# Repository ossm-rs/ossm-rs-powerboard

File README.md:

# OSSM-RS Powerboard

Power management PCB for AIM family motors, designed to pair with the Industrial ESP32-S3-RS485-CAN control board by Waveshare and run with OSSM-RS software.

This board is inspired by and builds on the OSSM hardware concept from KinkyMakers:
- OSSM-RS software: https://github.com/ossm-rs/ossm
- Original OSSM hardware/research: https://github.com/KinkyMakers/OSSM-hardware/tree/main

## What This Board Does

- Accepts DC input from an external power supply.
- Provides 24-36v output for the servo motor.
- Protects from back EMF.
- Provides regulated 12V output for the controller board.
- Supports two input connector variants in this repository:
	- C6P input variant (Molex-style connector).
	- R7BF input variant (barrel jack style, Kycon KPJX-4S).

## System

- Motor family:
	- 60aim40F
	- 57aim30
- Controller:
	- Waveshare Industrial ESP32-S3-RS485-CAN
- PSU
    - Meanwell GST220A36-R7BF
    - Meanwell GST360A36-C6P

Other motor configurations that use 24-36V may also work, but they have not been validated on this board yet.

## Board Variants

- C6P variant:
	- Input connector: C6P 6 Pin Molex footprint
	- Fabrication files prefix: `C6P_*`
	- STEP model: `STEP/powerboard-C6P.step`
- R7BF variant:
	- Input connector: R7BF KPJX-4S footprint
	- Fabrication files prefix: `R7BF_*`
	- STEP model: `STEP/powerboard-R7BF.step`

Do not populate both input connector styles on the same board.

## Usage

- External PSU (C6P or R7BF style) feeds the selected DC-IN connector on this board.
- Motor power is provided at the Motor Power output terminal.
- 12V and GND for the Waveshare board are provided at the ESP/CAN power terminal.
- Motor control and comms (CAN/RS485) are handled by the Waveshare board and motor harness.
- Configure and run OSSM-RS from https://github.com/ossm-rs/ossm.

Use the wiring diagram image below and verify polarity before first power-up.

## Manufacturing

For assembly orders, use files in `jlcpcb-fabrication-files/`:
- `*_bom.csv` for component list
- `*_positions.csv` for pick-and-place positions

This project is intended for small community group buys through JLCPCB (or another PCB manufacturer). As of 2026-03-17, a typical minimum order on JLCPCB is 5 boards and costs about EUR 100 total.

Estimated cost per board:
- PCB-only share: about EUR 20 per board (EUR 100 / 5)
- With shipping split across 5 boards: about (EUR 100 + shipping) / 5 per board

## Safety Notes

- This is a high-current motor power board; incorrect wiring can damage electronics.
- Always verify connector pinout/polarity against schematic and wiring diagrams.
- Keep wiring secure and strain-relieved.

## Credits

- OSSM-RS maintainers and contributors
- KinkyMakers OSSM hardware project and community research

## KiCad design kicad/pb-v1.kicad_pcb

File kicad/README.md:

# KiCad Project

Primary design source for the OSSM-RS powerboard.

## Main Files

- `pb-v1.kicad_sch`: Schematic
- `pb-v1.kicad_pcb`: PCB layout
- `pb-v1.kicad_pro`: KiCad project file
- `pb-v1.csv`: Consolidated BOM/export snapshot

## Project Libraries

- `project_symbols/`: Custom symbol libraries
- `project_footprints/`: Custom footprints
- `project_3dshapes/`: 3D models used by footprints

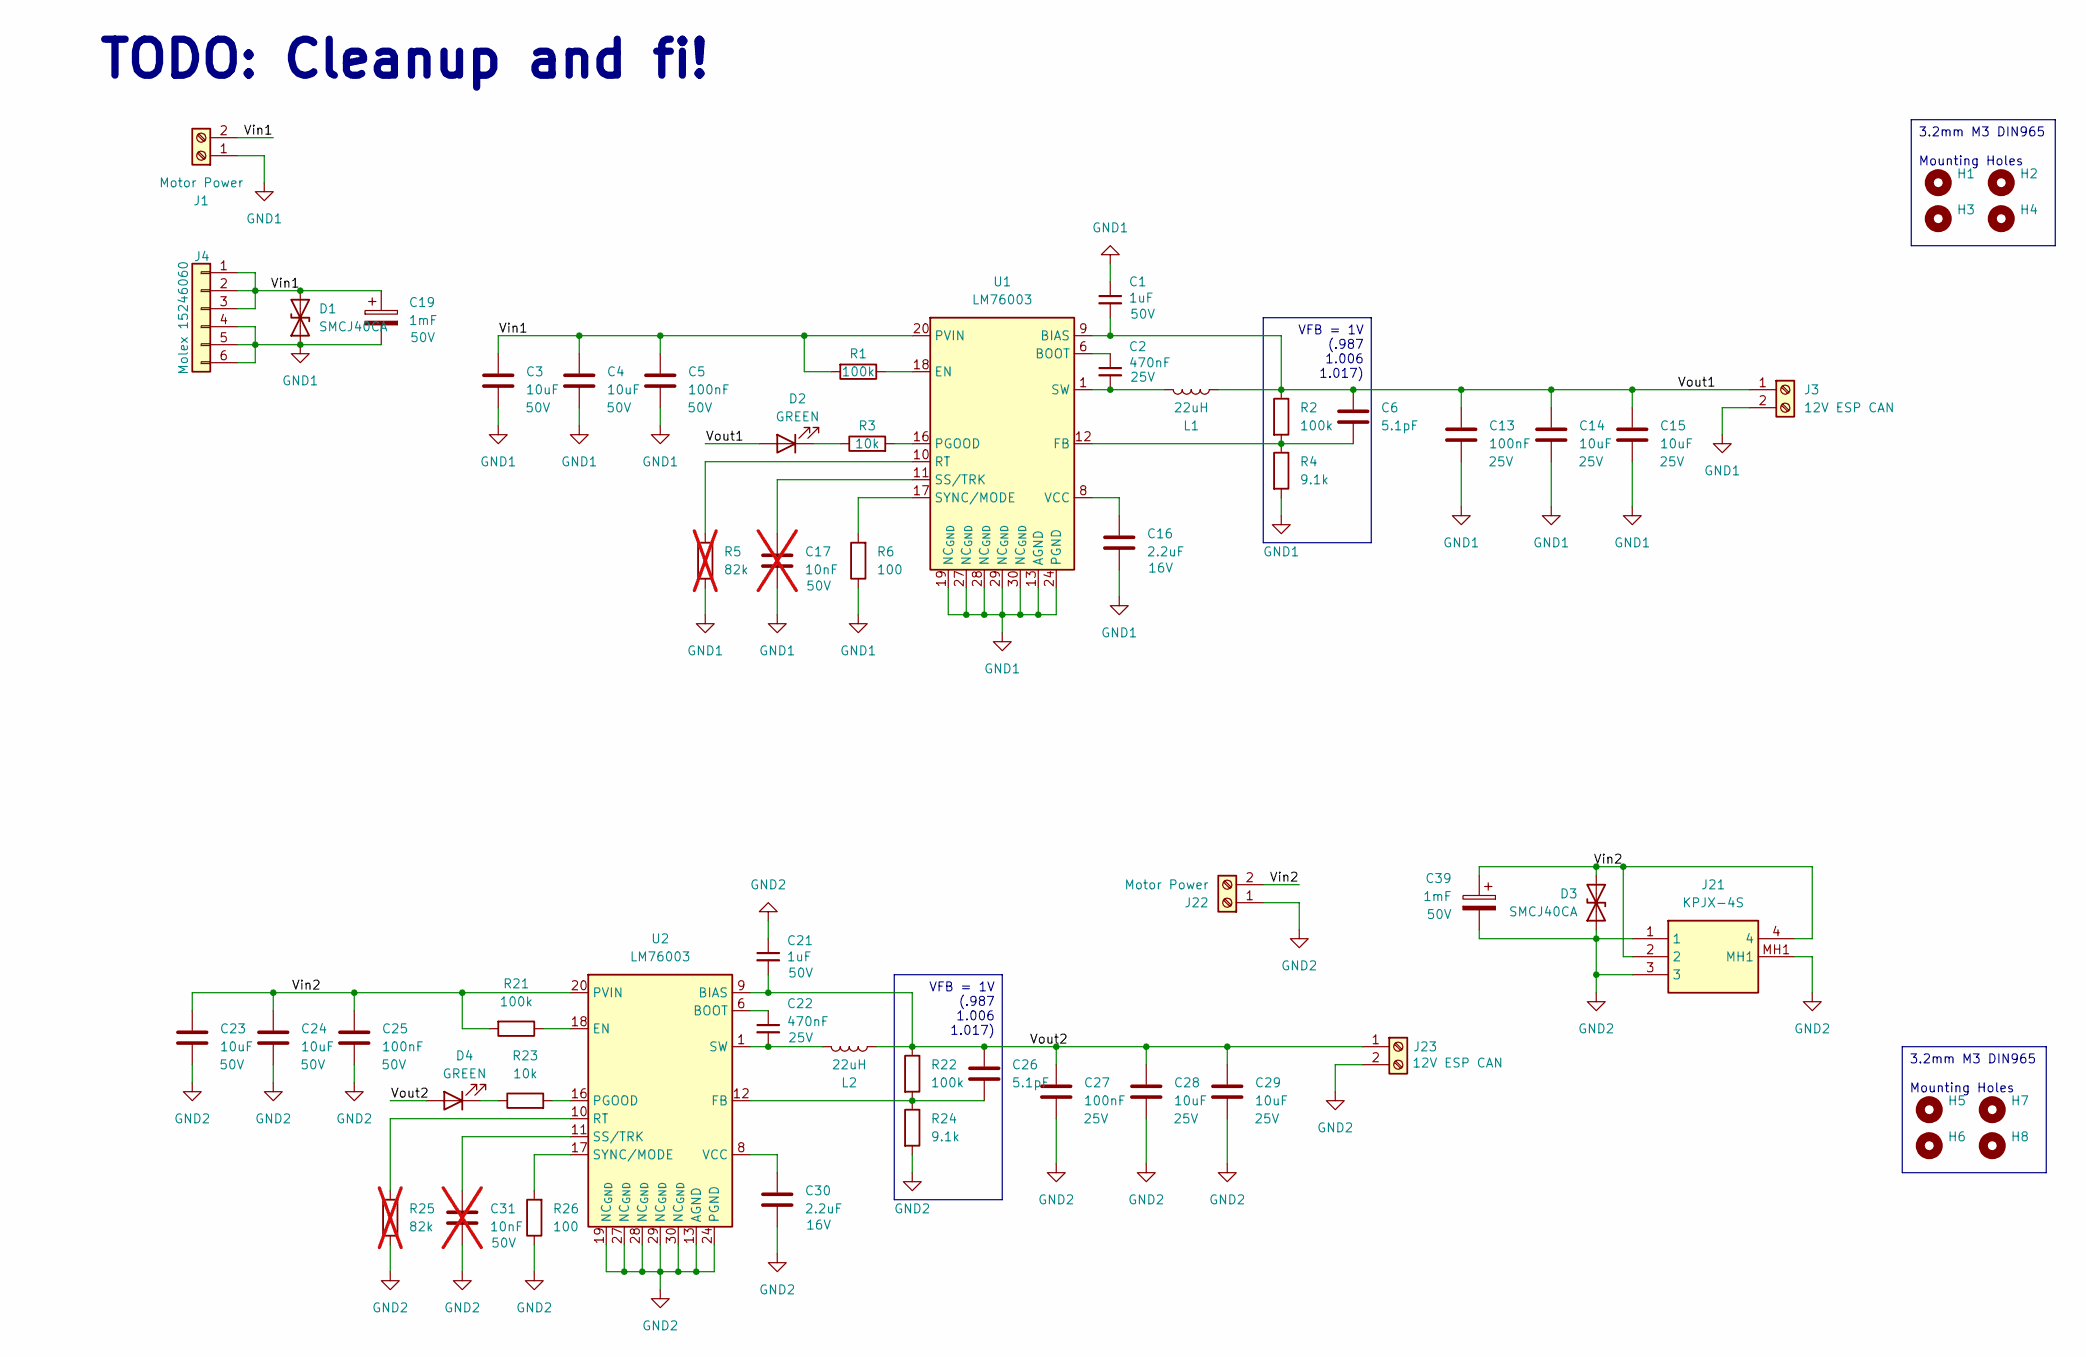
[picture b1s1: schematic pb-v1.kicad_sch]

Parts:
C1, C21: 1uF; C_0603_1608Metric; Voltage 50V; MPN C15849
C2, C22: 470nF; C_0603_1608Metric; Voltage 25V; MPN C1623
C3, C4, C23, C24: 10uF; C_1206_3216Metric; Voltage 50V; MPN C89632
C5, C25: 100nF; C_0603_1608Metric; Voltage 50V; MPN C14663
C6, C26: 5.1pF; C_0603_1608Metric; MPN C61816
C13, C27: 100nF; C_0603_1608Metric; Voltage 25V; MPN C14663
C14, C15, C28, C29: 10uF; C_1206_3216Metric; Voltage 25V; MPN C89632
C16, C30: 2.2uF; C_0603_1608Metric; Voltage 16V; MPN C23630
C17, C31: 10nF; C_0603_1608Metric; Voltage 50V; MPN C57112; not fitted
C19, C39: 1mF; CP_Elec_16x17.5; Voltage 50V; MPN C2164559
D1, D3: SMCJ40CA; D_SMC; MPN C80273
D2, D4: GREEN; LED_0603_1608Metric; MPN C12065
H1, H2, H3, H4, H5, H6, H7, H8: MountingHole; MountingHole_3.2mm_M3_DIN965
J1, J22: Motor Power; TerminalBlock_Phoenix_MKDS-1,5-2-5.08_1x02_P5.08mm_Horizont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; MPN C8465
J3, J23: 12V ESP CAN; TerminalBlock_Phoenix_PT-1,5-2-3.5-H_1x02_P3.50mm_Horizontal; MPN C466970
J4: Molex 15246060; CONN_SDA-42404_06_MOL; MPN C563687
J21: KPJX-4S; KPJX4S; Manufacturer_Part_Number KPJX-4S; Mouser Part Number 806-KPJX-4S
L1, L2: 22uH; L_Wurth_WE-PD-1050P; MPN C2651173
R1, R2, R21, R22: 100k; R_0603_1608Metric; MPN C25803
R3, R23: 10k; R_0603_1608Metric; MPN C25804
R4, R24: 9.1k; R_0603_1608Metric; MPN C23260
R5, R25: 82k; R_0603_1608Metric; MPN C23254; not fitted
R6, R26: 100; R_0603_1608Metric; MPN C22775
U1, U2: LM76003; Texas_RNP0030B_WQFN-30-1EP_4x6mm_P0.5mm_EP1.8x4.5mm_Thermal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; MPN C470958

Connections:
/Vin1: C3.1, C4.1, C5.1, C19.1, D1.2 (A2), J1.2, J4.1, J4.2, J4.3, R1.2, U1.20 (PVIN), U1.21 (PVIN), U1.22 (PVIN)
/Vin2: C23.1, C24.1, C25.1, C39.1, D3.2 (A2), J21.2, J21.4, J22.2, R21.2, U2.20 (PVIN), U2.21 (PVIN), U2.22 (PVIN)
/Vout1: C1.2, C6.1, C13.1, C14.1, C15.1, D2.2 (A), J3.1, L1.2, R2.1, U1.9 (BIAS)
/Vout2: C21.2, C26.1, C27.1, C28.1, C29.1, D4.2 (A), J23.1, L2.2, R22.1, U2.9 (BIAS)
GND1: C1.1, C3.2, C4.2, C5.2, C13.2, C14.2, C15.2, C16.2, C17.2, C19.2, D1.1 (A1), J1.1, J3.2, J4.4, J4.5, J4.6, R4.2, R5.1, R6.1, U1.13 (AGND), U1.14 (AGND), U1.15 (AGND), U1.19 (NC_{GND}), U1.24 (PGND), U1.25 (PGND), U1.26 (PGND), U1.27 (NC_{GND}), U1.28 (NC_{GND}), U1.29 (NC_{GND}), U1.30 (NC_{GND}), U1.31 (AGND)
GND2: C21.1, C23.2, C24.2, C25.2, C27.2, C28.2, C29.2, C30.2, C31.2, C39.2, D3.1 (A1), J21.1, J21.3, J21.MH1, J22.1, J23.2, R24.2, R25.1, R26.1, U2.13 (AGND), U2.14 (AGND), U2.15 (AGND), U2.19 (NC_{GND}), U2.24 (PGND), U2.25 (PGND), U2.26 (PGND), U2.27 (NC_{GND}), U2.28 (NC_{GND}), U2.29 (NC_{GND}), U2.30 (NC_{GND}), U2.31 (AGND)
unnamed: C2.2, L1.1, U1.1 (SW), U1.2 (SW), U1.3 (SW), U1.4 (SW), U1.5 (SW)
unnamed: C22.2, L2.1, U2.1 (SW), U2.2 (SW), U2.3 (SW), U2.4 (SW), U2.5 (SW)
unnamed: D2.1 (K), R3.1
unnamed: D4.1 (K), R23.1
unnamed: C2.1, U1.6 (BOOT)
unnamed: R1.1, U1.18 (EN)
unnamed: C6.2, R2.2, R4.1, U1.12 (FB)
unnamed: R3.2, U1.16 (PGOOD)
unnamed: R5.2, U1.10 (RT)
unnamed: C17.1, U1.11 (SS/TRK)
unnamed: R6.2, U1.17 (SYNC/MODE)
unnamed: C16.1, U1.8 (VCC)
unnamed: C22.1, U2.6 (BOOT)
unnamed: R21.1, U2.18 (EN)
unnamed: C26.2, R22.2, R24.1, U2.12 (FB)
unnamed: R23.2, U2.16 (PGOOD)
unnamed: R25.2, U2.10 (RT)
unnamed: C31.1, U2.11 (SS/TRK)
unnamed: R26.2, U2.17 (SYNC/MODE)
unnamed: C30.1, U2.8 (VCC)

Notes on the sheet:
TODO: Cleanup and fi!
VFB = 1V (.987 1.006 1.017)
3.2mm M3 DIN965 Mounting Holes

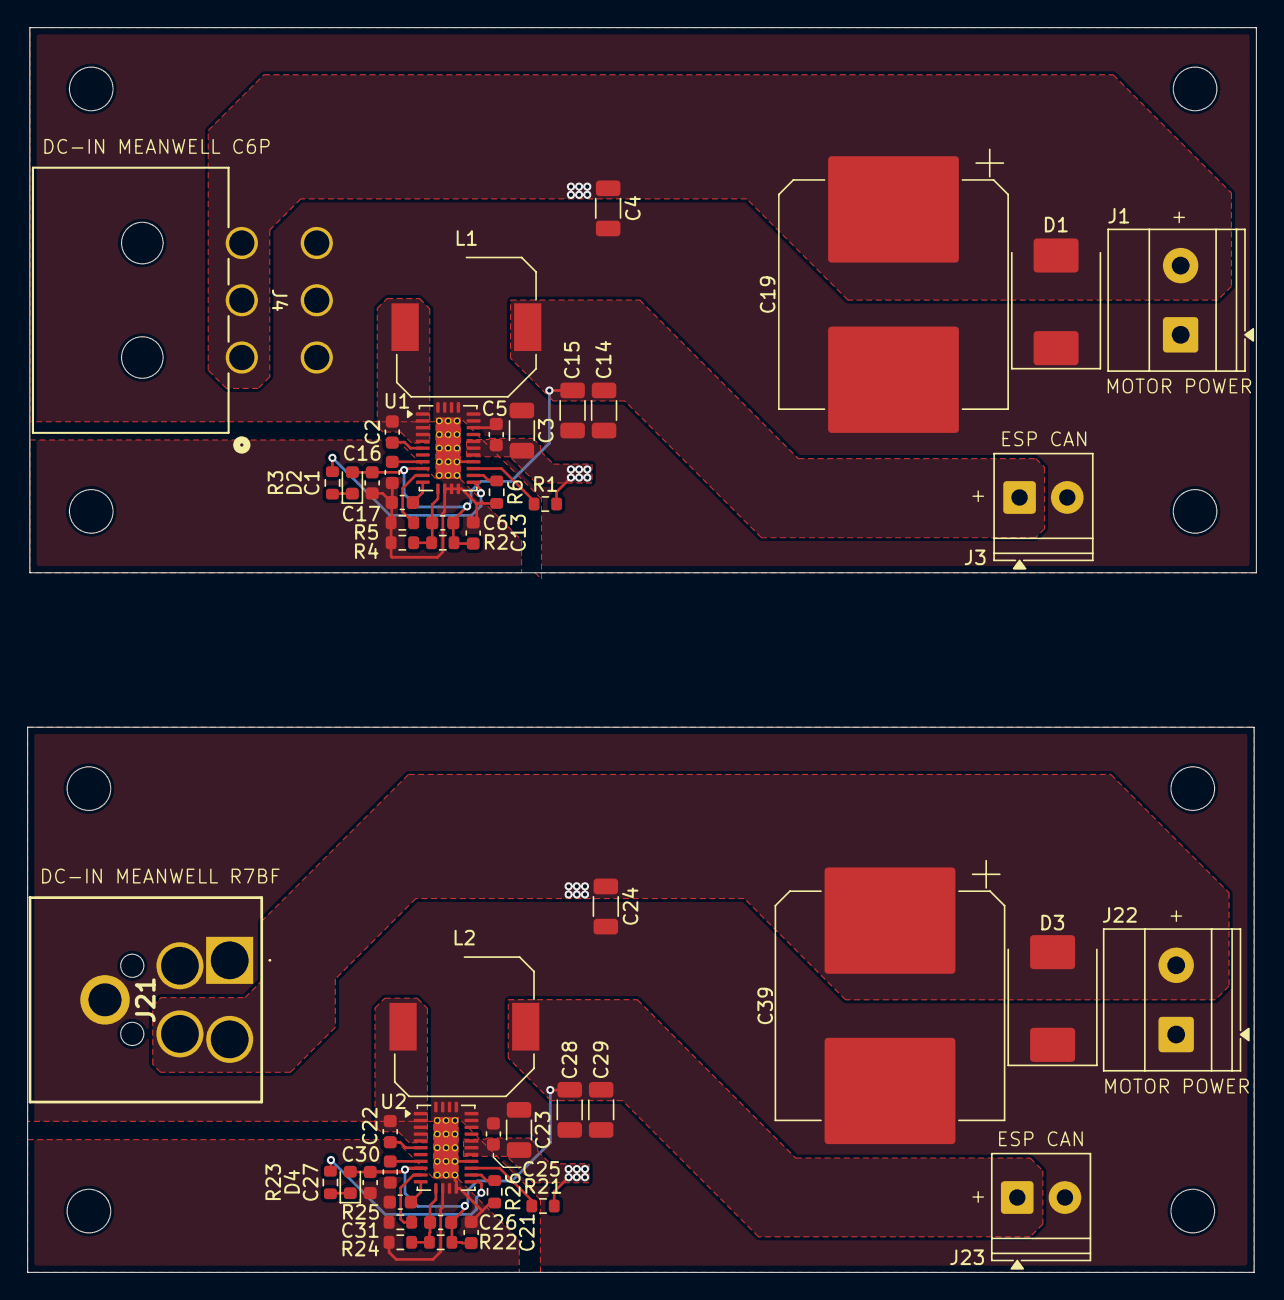
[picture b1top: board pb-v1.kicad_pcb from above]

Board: 2 copper layers, 90.2 x 91.3 mm, 58 parts (0 on the bottom side), 26 nets.

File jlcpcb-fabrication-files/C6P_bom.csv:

Designator,Footprint,Quantity,Value,LCSC Part #
C1,0603,1,1uF,C15849
"C13, C5",0603,2,100nF,C14663
"C14, C15, C3, C4",1206,4,10uF,C89632
C16,0603,1,2.2uF,C23630
C19,CP_Elec_16x17.5,1,1mF,C2164559
C2,0603,1,470nF,C1623
C6,0603,1,5.1pF,C61816
D1,D_SMC,1,SMCJ40CA,C80273
D2,0603,1,GREEN,C12065
J1,"TerminalBlock_Phoenix_MKDS-1,5-2-5.08_1x02_P5.08mm_Horizontal",1,Motor Power,C8465
J3,"TerminalBlock_Phoenix_PT-1,5-2-3.5-H_1x02_P3.50mm_Horizontal",1,12V ESP CAN,C466970
J4,CONN_SDA-42404_06_MOL,1,Molex 15246060,C563687
L1,L_Wurth_WE-PD-1050P,1,22uH,C2651173
"R1, R2",0603,2,100k,C25803
R3,0603,1,10k,C25804
R4,0603,1,9.1k,C23260
R6,0603,1,100,C22775
U1,Texas_RNP0030B_WQFN-30-1EP_4x6mm_P0.5mm_EP1.8x4.5mm_ThermalVias,1,LM76003,C470958

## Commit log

2026-03-17 Init repo
